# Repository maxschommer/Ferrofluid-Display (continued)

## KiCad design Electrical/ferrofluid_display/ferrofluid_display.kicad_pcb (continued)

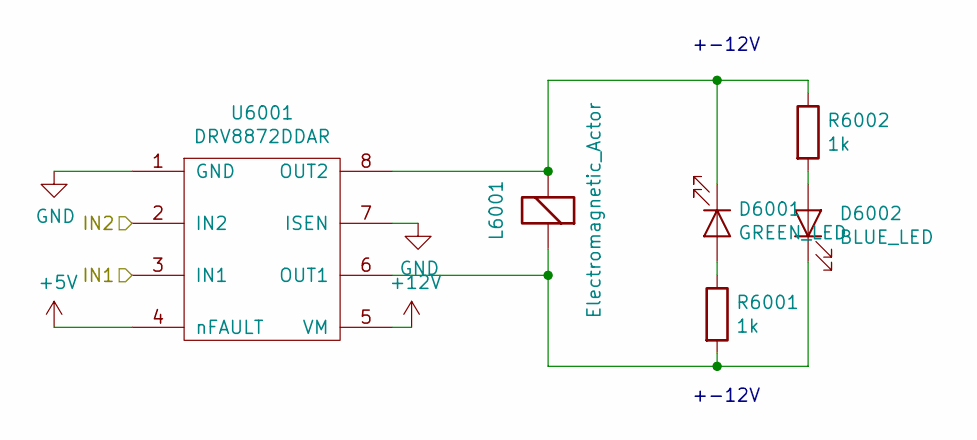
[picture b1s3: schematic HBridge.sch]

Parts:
D6001: GREEN_LED; LED_0805
D6002: BLUE_LED; LED_0805
L6001: Electromagnetic_Actor; ElectroMagnet
R6001, R6002: 1k; R_0603
U6001: DRV8872DDAR; TI_SO-PowerPAD-8_ThermalVias

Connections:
+5V: U6001.4 (nFAULT); also elsewhere on the board
+12V: U6001.5 (VM); also elsewhere on the board
/O_1: U6001.3 (IN1); also elsewhere on the board
/O_2: U6001.2 (IN2); also elsewhere on the board
GND: U6001.1 (GND), U6001.7 (ISEN); also elsewhere on the board
unnamed: D6001.1 (K), L6001.2 (+), R6002.1, U6001.8 (OUT2)
unnamed: D6001.2 (A), R6001.1
unnamed: D6002.1 (K), L6001.1 (-), R6001.2, U6001.6 (OUT1)
unnamed: D6002.2 (A), R6002.2

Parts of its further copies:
D7001, D8001, D9001, D10001, D11001, D12001, D13001, D14001, D15001, D17001, D18001, D19001, D20001, D21001, D22001, D23001, D24001, D25001, D26001, D28001, D29001, D30001, D31001, D32001, D33001, D34001, D35001, D36001, D37001, D39001, D40001, D41001, D42001, D43001, D44001, D45001, D46001, D47001, D48001, D50001, D51001, D52001, D53001, D54001, D55001, D56001, D57001, D58001, D59001, D61001, D62001, D63001, D64001, D65001, D66001, D67001, D68001, D69001, D70001, D72001, D73001, D74001, D75001, D76001, D77001, D78001, D79001, D80001, D81001, D83001, D84001, D85001, D86001, D87001, D88001, D89001, D90001, D91001, D92001, D94001, D95001, D96001, D97001, D98001, D99001, D100001, D101001, D102001, D103001, D105001, D106001, D107001, D108001, D109001, D110001, D111001, D112001, D113001, D114001: GREEN_LED; LED_0805
D7002, D8002, D9002, D10002, D11002, D12002, D13002, D14002, D15002, D17002, D18002, D19002, D20002, D21002, D22002, D23002, D24002, D25002, D26002, D28002, D29002, D30002, D31002, D32002, D33002, D34002, D35002, D36002, D37002, D39002, D40002, D41002, D42002, D43002, D44002, D45002, D46002, D47002, D48002, D50002, D51002, D52002, D53002, D54002, D55002, D56002, D57002, D58002, D59002, D61002, D62002, D63002, D64002, D65002, D66002, D67002, D68002, D69002, D70002, D72002, D73002, D74002, D75002, D76002, D77002, D78002, D79002, D80002, D81002, D83002, D84002, D85002, D86002, D87002, D88002, D89002, D90002, D91002, D92002, D94002, D95002, D96002, D97002, D98002, D99002, D100002, D101002, D102002, D103002, D105002, D106002, D107002, D108002, D109002, D110002, D111002, D112002, D113002, D114002: BLUE_LED; LED_0805
L7001, L8001, L9001, L10001, L11001, L12001, L13001, L14001, L15001, L17001, L18001, L19001, L20001, L21001, L22001, L23001, L24001, L25001, L26001, L28001, L29001, L30001, L31001, L32001, L33001, L34001, L35001, L36001, L37001, L39001, L40001, L41001, L42001, L43001, L44001, L45001, L46001, L47001, L48001, L50001, L51001, L52001, L53001, L54001, L55001, L56001, L57001, L58001, L59001, L61001, L62001, L63001, L64001, L65001, L66001, L67001, L68001, L69001, L70001, L72001, L73001, L74001, L75001, L76001, L77001, L78001, L79001, L80001, L81001, L83001, L84001, L85001, L86001, L87001, L88001, L89001, L90001, L91001, L92001, L94001, L95001, L96001, L97001, L98001, L99001, L100001, L101001, L102001, L103001, L105001, L106001, L107001, L108001, L109001, L110001, L111001, L112001, L113001, L114001: Electromagnetic_Actor; ElectroMagnet
R7001, R7002, R8001, R8002, R9001, R9002, R10001, R10002, R11001, R11002, R12001, R12002, R13001, R13002, R14001, R14002, R15001, R15002, R17001, R17002, R18001, R18002, R19001, R19002, R20001, R20002, R21001, R21002, R22001, R22002, R23001, R23002, R24001, R24002, R25001, R25002, R26001, R26002, R28001, R28002, R29001, R29002, R30001, R30002, R31001, R31002, R32001, R32002, R33001, R33002, R34001, R34002, R35001, R35002, R36001, R36002, R37001, R37002, R39001, R39002, R40001, R40002, R41001, R41002, R42001, R42002, R43001, R43002, R44001, R44002, R45001, R45002, R46001, R46002, R47001, R47002, R48001, R48002, R50001, R50002, R51001, R51002, R52001, R52002, R53001, R53002, R54001, R54002, R55001, R55002, R56001, R56002, R57001, R57002, R58001, R58002, R59001, R59002, R61001, R61002, R62001, R62002, R63001, R63002, R64001, R64002, R65001, R65002, R66001, R66002, R67001, R67002, R68001, R68002, R69001, R69002, R70001, R70002, R72001, R72002, R73001, R73002, R74001, R74002, R75001, R75002, R76001, R76002, R77001, R77002, R78001, R78002, R79001, R79002, R80001, R80002, R81001, R81002, R83001, R83002, R84001, R84002, R85001, R85002, R86001, R86002, R87001, R87002, R88001, R88002, R89001, R89002, R90001, R90002, R91001, R91002, R92001, R92002, R94001, R94002, R95001, R95002, R96001, R96002, R97001, R97002, R98001, R98002, R99001, R99002, R100001, R100002, R101001, R101002, R102001, R102002, R103001, R103002, R105001, R105002, R106001, R106002, R107001, R107002, R108001, R108002, R109001, R109002, R110001, R110002, R111001, R111002, R112001, R112002, R113001, R113002, R114001, R114002: 1k; R_0603
U7001, U8001, U9001, U10001, U11001, U12001, U13001, U14001, U15001, U17001, U18001, U19001, U20001, U21001, U22001, U23001, U24001, U25001, U26001, U28001, U29001, U30001, U31001, U32001, U33001, U34001, U35001, U36001, U37001, U39001, U40001, U41001, U42001, U43001, U44001, U45001, U46001, U47001, U48001, U50001, U51001, U52001, U53001, U54001, U55001, U56001, U57001, U58001, U59001, U61001, U62001, U63001, U64001, U65001, U66001, U67001, U68001, U69001, U70001, U72001, U73001, U74001, U75001, U76001, U77001, U78001, U79001, U80001, U81001, U83001, U84001, U85001, U86001, U87001, U88001, U89001, U90001, U91001, U92001, U94001, U95001, U96001, U97001, U98001, U99001, U100001, U101001, U102001, U103001, U105001, U106001, U107001, U108001, U109001, U110001, U111001, U112001, U113001, U114001: DRV8872DDAR; TI_SO-PowerPAD-8_ThermalVias

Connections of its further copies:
+5V: U7001.4 (nFAULT), U8001.4 (nFAULT), U9001.4 (nFAULT), U10001.4 (nFAULT), U11001.4 (nFAULT), U12001.4 (nFAULT), U13001.4 (nFAULT), U14001.4 (nFAULT), U15001.4 (nFAULT), U17001.4 (nFAULT), U18001.4 (nFAULT), U19001.4 (nFAULT), U20001.4 (nFAULT), U21001.4 (nFAULT), U22001.4 (nFAULT), U23001.4 (nFAULT), U24001.4 (nFAULT), U25001.4 (nFAULT), U26001.4 (nFAULT), U28001.4 (nFAULT), U29001.4 (nFAULT), U30001.4 (nFAULT), U31001.4 (nFAULT), U32001.4 (nFAULT), U33001.4 (nFAULT), U34001.4 (nFAULT), U35001.4 (nFAULT), U36001.4 (nFAULT), U37001.4 (nFAULT), U39001.4 (nFAULT), U40001.4 (nFAULT), U41001.4 (nFAULT), U42001.4 (nFAULT), U43001.4 (nFAULT), U44001.4 (nFAULT), U45001.4 (nFAULT), U46001.4 (nFAULT), U47001.4 (nFAULT), U48001.4 (nFAULT), U50001.4 (nFAULT), U51001.4 (nFAULT), U52001.4 (nFAULT), U53001.4 (nFAULT), U54001.4 (nFAULT), U55001.4 (nFAULT), U56001.4 (nFAULT), U57001.4 (nFAULT), U58001.4 (nFAULT), U59001.4 (nFAULT), U61001.4 (nFAULT), U62001.4 (nFAULT), U63001.4 (nFAULT), U64001.4 (nFAULT), U65001.4 (nFAULT), U66001.4 (nFAULT), U67001.4 (nFAULT), U68001.4 (nFAULT), U69001.4 (nFAULT), U70001.4 (nFAULT), U72001.4 (nFAULT), U73001.4 (nFAULT), U74001.4 (nFAULT), U75001.4 (nFAULT), U76001.4 (nFAULT), U77001.4 (nFAULT), U78001.4 (nFAULT), U79001.4 (nFAULT), U80001.4 (nFAULT), U81001.4 (nFAULT), U83001.4 (nFAULT), U84001.4 (nFAULT), U85001.4 (nFAULT), U86001.4 (nFAULT), U87001.4 (nFAULT), U88001.4 (nFAULT), U89001.4 (nFAULT), U90001.4 (nFAULT), U91001.4 (nFAULT), U92001.4 (nFAULT), U94001.4 (nFAULT), U95001.4 (nFAULT), U96001.4 (nFAULT), U97001.4 (nFAULT), U98001.4 (nFAULT), U99001.4 (nFAULT), U100001.4 (nFAULT), U101001.4 (nFAULT), U102001.4 (nFAULT), U103001.4 (nFAULT), U105001.4 (nFAULT), U106001.4 (nFAULT), U107001.4 (nFAULT), U108001.4 (nFAULT), U109001.4 (nFAULT), U110001.4 (nFAULT), U111001.4 (nFAULT), U112001.4 (nFAULT), U113001.4 (nFAULT), U114001.4 (nFAULT); also elsewhere on the board
+12V: U7001.5 (VM), U8001.5 (VM), U9001.5 (VM), U10001.5 (VM), U11001.5 (VM), U12001.5 (VM), U13001.5 (VM), U14001.5 (VM), U15001.5 (VM), U17001.5 (VM), U18001.5 (VM), U19001.5 (VM), U20001.5 (VM), U21001.5 (VM), U22001.5 (VM), U23001.5 (VM), U24001.5 (VM), U25001.5 (VM), U26001.5 (VM), U28001.5 (VM), U29001.5 (VM), U30001.5 (VM), U31001.5 (VM), U32001.5 (VM), U33001.5 (VM), U34001.5 (VM), U35001.5 (VM), U36001.5 (VM), U37001.5 (VM), U39001.5 (VM), U40001.5 (VM), U41001.5 (VM), U42001.5 (VM), U43001.5 (VM), U44001.5 (VM), U45001.5 (VM), U46001.5 (VM), U47001.5 (VM), U48001.5 (VM), U50001.5 (VM), U51001.5 (VM), U52001.5 (VM), U53001.5 (VM), U54001.5 (VM), U55001.5 (VM), U56001.5 (VM), U57001.5 (VM), U58001.5 (VM), U59001.5 (VM), U61001.5 (VM), U62001.5 (VM), U63001.5 (VM), U64001.5 (VM), U65001.5 (VM), U66001.5 (VM), U67001.5 (VM), U68001.5 (VM), U69001.5 (VM), U70001.5 (VM), U72001.5 (VM), U73001.5 (VM), U74001.5 (VM), U75001.5 (VM), U76001.5 (VM), U77001.5 (VM), U78001.5 (VM), U79001.5 (VM), U80001.5 (VM), U81001.5 (VM), U83001.5 (VM), U84001.5 (VM), U85001.5 (VM), U86001.5 (VM), U87001.5 (VM), U88001.5 (VM), U89001.5 (VM), U90001.5 (VM), U91001.5 (VM), U92001.5 (VM), U94001.5 (VM), U95001.5 (VM), U96001.5 (VM), U97001.5 (VM), U98001.5 (VM), U99001.5 (VM), U100001.5 (VM), U101001.5 (VM), U102001.5 (VM), U103001.5 (VM), U105001.5 (VM), U106001.5 (VM), U107001.5 (VM), U108001.5 (VM), U109001.5 (VM), U110001.5 (VM), U111001.5 (VM), U112001.5 (VM), U113001.5 (VM), U114001.5 (VM); also elsewhere on the board
/O_3: U7001.3 (IN1); also elsewhere on the board
/O_4: U7001.2 (IN2); also elsewhere on the board
/O_5: U8001.3 (IN1); also elsewhere on the board
/O_6: U8001.2 (IN2); also elsewhere on the board
/O_7: U9001.3 (IN1); also elsewhere on the board
/O_8: U9001.2 (IN2); also elsewhere on the board
/O_9: U10001.3 (IN1); also elsewhere on the board
/O_10: U10001.2 (IN2); also elsewhere on the board
/O_11: U11001.3 (IN1); also elsewhere on the board
/O_12: U11001.2 (IN2); also elsewhere on the board
/O_13: U12001.3 (IN1); also elsewhere on the board
/O_14: U12001.2 (IN2); also elsewhere on the board
/O_15: U13001.3 (IN1); also elsewhere on the board
/O_16: U13001.2 (IN2); also elsewhere on the board
/O_17: U14001.3 (IN1); also elsewhere on the board
/O_18: U14001.2 (IN2); also elsewhere on the board
/O_19: U15001.3 (IN1); also elsewhere on the board
/O_20: U15001.2 (IN2); also elsewhere on the board
/O_21: U61001.3 (IN1); also elsewhere on the board
/O_22: U61001.2 (IN2); also elsewhere on the board
/O_23: U62001.3 (IN1); also elsewhere on the board
/O_24: U62001.2 (IN2); also elsewhere on the board
/O_25: U63001.3 (IN1); also elsewhere on the board
/O_26: U63001.2 (IN2); also elsewhere on the board
/O_27: U64001.3 (IN1); also elsewhere on the board
/O_28: U64001.2 (IN2); also elsewhere on the board
/O_29: U65001.3 (IN1); also elsewhere on the board
/O_30: U65001.2 (IN2); also elsewhere on the board
/O_31: U66001.3 (IN1); also elsewhere on the board
/O_32: U66001.2 (IN2); also elsewhere on the board
/O_33: U67001.3 (IN1); also elsewhere on the board
/O_34: U67001.2 (IN2); also elsewhere on the board
/O_35: U68001.3 (IN1); also elsewhere on the board
/O_36: U68001.2 (IN2); also elsewhere on the board
/O_37: U69001.3 (IN1); also elsewhere on the board
/O_38: U69001.2 (IN2); also elsewhere on the board
/O_39: U70001.3 (IN1); also elsewhere on the board
/O_40: U70001.2 (IN2); also elsewhere on the board
/O_41: U17001.3 (IN1); also elsewhere on the board
/O_42: U17001.2 (IN2); also elsewhere on the board
/O_43: U18001.3 (IN1); also elsewhere on the board
/O_44: U18001.2 (IN2); also elsewhere on the board
/O_45: U19001.3 (IN1); also elsewhere on the board
/O_46: U19001.2 (IN2); also elsewhere on the board
/O_47: U20001.3 (IN1); also elsewhere on the board
/O_48: U20001.2 (IN2); also elsewhere on the board
/O_49: U21001.3 (IN1); also elsewhere on the board
/O_50: U21001.2 (IN2); also elsewhere on the board
/O_51: U22001.3 (IN1); also elsewhere on the board
/O_52: U22001.2 (IN2); also elsewhere on the board
/O_53: U23001.3 (IN1); also elsewhere on the board
/O_54: U23001.2 (IN2); also elsewhere on the board
/O_55: U24001.3 (IN1); also elsewhere on the board
/O_56: U24001.2 (IN2); also elsewhere on the board
/O_57: U25001.3 (IN1); also elsewhere on the board
/O_58: U25001.2 (IN2); also elsewhere on the board
/O_59: U26001.3 (IN1); also elsewhere on the board
/O_60: U26001.2 (IN2); also elsewhere on the board
/O_61: U72001.3 (IN1); also elsewhere on the board
/O_62: U72001.2 (IN2); also elsewhere on the board
/O_63: U73001.3 (IN1); also elsewhere on the board
/O_64: U73001.2 (IN2); also elsewhere on the board
/O_65: U74001.3 (IN1); also elsewhere on the board
/O_66: U74001.2 (IN2); also elsewhere on the board
/O_67: U75001.3 (IN1); also elsewhere on the board
/O_68: U75001.2 (IN2); also elsewhere on the board
/O_69: U76001.3 (IN1); also elsewhere on the board
/O_70: U76001.2 (IN2); also elsewhere on the board
/O_71: U77001.3 (IN1); also elsewhere on the board
/O_72: U77001.2 (IN2); also elsewhere on the board
/O_73: U78001.3 (IN1); also elsewhere on the board
/O_74: U78001.2 (IN2); also elsewhere on the board
/O_75: U79001.3 (IN1); also elsewhere on the board
/O_76: U79001.2 (IN2); also elsewhere on the board
/O_77: U80001.3 (IN1); also elsewhere on the board
/O_78: U80001.2 (IN2); also elsewhere on the board
/O_79: U81001.3 (IN1); also elsewhere on the board
/O_80: U81001.2 (IN2); also elsewhere on the board
/O_81: U28001.3 (IN1); also elsewhere on the board
/O_82: U28001.2 (IN2); also elsewhere on the board
/O_83: U29001.3 (IN1); also elsewhere on the board
/O_84: U29001.2 (IN2); also elsewhere on the board
/O_85: U30001.3 (IN1); also elsewhere on the board
/O_86: U30001.2 (IN2); also elsewhere on the board
/O_87: U31001.3 (IN1); also elsewhere on the board
/O_88: U31001.2 (IN2); also elsewhere on the board
/O_89: U32001.3 (IN1); also elsewhere on the board
/O_90: U32001.2 (IN2); also elsewhere on the board
/O_91: U33001.3 (IN1); also elsewhere on the board
/O_92: U33001.2 (IN2); also elsewhere on the board
/O_93: U34001.3 (IN1); also elsewhere on the board
/O_94: U34001.2 (IN2); also elsewhere on the board
/O_95: U35001.3 (IN1); also elsewhere on the board
/O_96: U35001.2 (IN2); also elsewhere on the board
/O_97: U36001.3 (IN1); also elsewhere on the board
/O_98: U36001.2 (IN2); also elsewhere on the board
/O_99: U37001.3 (IN1); also elsewhere on the board
/O_100: U37001.2 (IN2); also elsewhere on the board
/O_101: U83001.3 (IN1); also elsewhere on the board
/O_102: U83001.2 (IN2); also elsewhere on the board
/O_103: U84001.3 (IN1); also elsewhere on the board
/O_104: U84001.2 (IN2); also elsewhere on the board
/O_105: U85001.3 (IN1); also elsewhere on the board
/O_106: U85001.2 (IN2); also elsewhere on the board
/O_107: U86001.3 (IN1); also elsewhere on the board
/O_108: U86001.2 (IN2); also elsewhere on the board
/O_109: U87001.3 (IN1); also elsewhere on the board
/O_110: U87001.2 (IN2); also elsewhere on the board
/O_111: U88001.3 (IN1); also elsewhere on the board
/O_112: U88001.2 (IN2); also elsewhere on the board
/O_113: U89001.3 (IN1); also elsewhere on the board
/O_114: U89001.2 (IN2); also elsewhere on the board
/O_115: U90001.3 (IN1); also elsewhere on the board
/O_116: U90001.2 (IN2); also elsewhere on the board
/O_117: U91001.3 (IN1); also elsewhere on the board
/O_118: U91001.2 (IN2); also elsewhere on the board
/O_119: U92001.3 (IN1); also elsewhere on the board
/O_120: U92001.2 (IN2); also elsewhere on the board
/O_121: U39001.3 (IN1); also elsewhere on the board
/O_122: U39001.2 (IN2); also elsewhere on the board
/O_123: U40001.3 (IN1); also elsewhere on the board
/O_124: U40001.2 (IN2); also elsewhere on the board
/O_125: U41001.3 (IN1); also elsewhere on the board
/O_126: U41001.2 (IN2); also elsewhere on the board
/O_127: U42001.3 (IN1); also elsewhere on the board
/O_128: U42001.2 (IN2); also elsewhere on the board
/O_129: U43001.3 (IN1); also elsewhere on the board
/O_130: U43001.2 (IN2); also elsewhere on the board
/O_131: U44001.3 (IN1); also elsewhere on the board
/O_132: U44001.2 (IN2); also elsewhere on the board
/O_133: U45001.3 (IN1); also elsewhere on the board
/O_134: U45001.2 (IN2); also elsewhere on the board
/O_135: U46001.3 (IN1); also elsewhere on the board
/O_136: U46001.2 (IN2); also elsewhere on the board
/O_137: U47001.3 (IN1); also elsewhere on the board
/O_138: U47001.2 (IN2); also elsewhere on the board
/O_139: U48001.3 (IN1); also elsewhere on the board
/O_140: U48001.2 (IN2); also elsewhere on the board
/O_141: U94001.3 (IN1); also elsewhere on the board
/O_142: U94001.2 (IN2); also elsewhere on the board
/O_143: U95001.3 (IN1); also elsewhere on the board
/O_144: U95001.2 (IN2); also elsewhere on the board
/O_145: U96001.3 (IN1); also elsewhere on the board
/O_146: U96001.2 (IN2); also elsewhere on the board
/O_147: U97001.3 (IN1); also elsewhere on the board
/O_148: U97001.2 (IN2); also elsewhere on the board
/O_149: U98001.3 (IN1); also elsewhere on the board
/O_150: U98001.2 (IN2); also elsewhere on the board
/O_151: U99001.3 (IN1); also elsewhere on the board
/O_152: U99001.2 (IN2); also elsewhere on the board
/O_153: U100001.3 (IN1); also elsewhere on the board
/O_154: U100001.2 (IN2); also elsewhere on the board
/O_155: U101001.3 (IN1); also elsewhere on the board
/O_156: U101001.2 (IN2); also elsewhere on the board
/O_157: U102001.3 (IN1); also elsewhere on the board
/O_158: U102001.2 (IN2); also elsewhere on the board
/O_159: U103001.3 (IN1); also elsewhere on the board
/O_160: U103001.2 (IN2); also elsewhere on the board
/O_161: U50001.3 (IN1); also elsewhere on the board
/O_162: U50001.2 (IN2); also elsewhere on the board
/O_163: U51001.3 (IN1); also elsewhere on the board
/O_164: U51001.2 (IN2); also elsewhere on the board
/O_165: U52001.3 (IN1); also elsewhere on the board
/O_166: U52001.2 (IN2); also elsewhere on the board
/O_167: U53001.3 (IN1); also elsewhere on the board
/O_168: U53001.2 (IN2); also elsewhere on the board
/O_169: U54001.3 (IN1); also elsewhere on the board
/O_170: U54001.2 (IN2); also elsewhere on the board
/O_171: U55001.3 (IN1); also elsewhere on the board
/O_172: U55001.2 (IN2); also elsewhere on the board
/O_173: U56001.3 (IN1); also elsewhere on the board
/O_174: U56001.2 (IN2); also elsewhere on the board
/O_175: U57001.3 (IN1); also elsewhere on the board
/O_176: U57001.2 (IN2); also elsewhere on the board
/O_177: U58001.3 (IN1); also elsewhere on the board
/O_178: U58001.2 (IN2); also elsewhere on the board
/O_179: U59001.3 (IN1); also elsewhere on the board
/O_180: U59001.2 (IN2); also elsewhere on the board
/O_181: U105001.3 (IN1); also elsewhere on the board
/O_182: U105001.2 (IN2); also elsewhere on the board
/O_183: U106001.3 (IN1); also elsewhere on the board
/O_184: U106001.2 (IN2); also elsewhere on the board
/O_185: U107001.3 (IN1); also elsewhere on the board
/O_186: U107001.2 (IN2); also elsewhere on the board
/O_187: U108001.3 (IN1); also elsewhere on the board
/O_188: U108001.2 (IN2); also elsewhere on the board
/O_189: U109001.3 (IN1); also elsewhere on the board
/O_190: U109001.2 (IN2); also elsewhere on the board
/O_191: U110001.3 (IN1); also elsewhere on the board
/O_192: U110001.2 (IN2); also elsewhere on the board
/O_193: U111001.3 (IN1); also elsewhere on the board
/O_194: U111001.2 (IN2); also elsewhere on the board
/O_195: U112001.3 (IN1); also elsewhere on the board
/O_196: U112001.2 (IN2); also elsewhere on the board
/O_197: U113001.3 (IN1); also elsewhere on the board
/O_198: U113001.2 (IN2); also elsewhere on the board
/O_199: U114001.3 (IN1); also elsewhere on the board
/O_200: U114001.2 (IN2); also elsewhere on the board
GND: U7001.1 (GND), U7001.7 (ISEN), U8001.1 (GND), U8001.7 (ISEN), U9001.1 (GND), U9001.7 (ISEN), U10001.1 (GND), U10001.7 (ISEN), U11001.1 (GND), U11001.7 (ISEN), U12001.1 (GND), U12001.7 (ISEN), U13001.1 (GND), U13001.7 (ISEN), U14001.1 (GND), U14001.7 (ISEN), U15001.1 (GND), U15001.7 (ISEN), U17001.1 (GND), U17001.7 (ISEN), U18001.1 (GND), U18001.7 (ISEN), U19001.1 (GND), U19001.7 (ISEN), U20001.1 (GND), U20001.7 (ISEN), U21001.1 (GND), U21001.7 (ISEN), U22001.1 (GND), U22001.7 (ISEN), U23001.1 (GND), U23001.7 (ISEN), U24001.1 (GND), U24001.7 (ISEN), U25001.1 (GND), U25001.7 (ISEN), U26001.1 (GND), U26001.7 (ISEN), U28001.1 (GND), U28001.7 (ISEN), U29001.1 (GND), U29001.7 (ISEN), U30001.1 (GND), U30001.7 (ISEN), U31001.1 (GND), U31001.7 (ISEN), U32001.1 (GND), U32001.7 (ISEN), U33001.1 (GND), U33001.7 (ISEN), U34001.1 (GND), U34001.7 (ISEN), U35001.1 (GND), U35001.7 (ISEN), U36001.1 (GND), U36001.7 (ISEN), U37001.1 (GND), U37001.7 (ISEN), U39001.1 (GND), U39001.7 (ISEN), U40001.1 (GND), U40001.7 (ISEN), U41001.1 (GND), U41001.7 (ISEN), U42001.1 (GND), U42001.7 (ISEN), U43001.1 (GND), U43001.7 (ISEN), U44001.1 (GND), U44001.7 (ISEN), U45001.1 (GND), U45001.7 (ISEN), U46001.1 (GND), U46001.7 (ISEN), U47001.1 (GND), U47001.7 (ISEN), U48001.1 (GND), U48001.7 (ISEN), U50001.1 (GND), U50001.7 (ISEN), U51001.1 (GND), U51001.7 (ISEN), U52001.1 (GND), U52001.7 (ISEN), U53001.1 (GND), U53001.7 (ISEN), U54001.1 (GND), U54001.7 (ISEN), U55001.1 (GND), U55001.7 (ISEN), U56001.1 (GND), U56001.7 (ISEN), U57001.1 (GND), U57001.7 (ISEN), U58001.1 (GND), U58001.7 (ISEN), U59001.1 (GND), U59001.7 (ISEN), U61001.1 (GND), U61001.7 (ISEN), U62001.1 (GND), U62001.7 (ISEN), U63001.1 (GND), U63001.7 (ISEN), U64001.1 (GND), U64001.7 (ISEN), U65001.1 (GND), U65001.7 (ISEN), U66001.1 (GND), U66001.7 (ISEN), U67001.1 (GND), U67001.7 (ISEN), U68001.1 (GND), U68001.7 (ISEN), U69001.1 (GND), U69001.7 (ISEN), U70001.1 (GND), U70001.7 (ISEN), U72001.1 (GND), U72001.7 (ISEN), U73001.1 (GND), U73001.7 (ISEN), U74001.1 (GND), U74001.7 (ISEN), U75001.1 (GND), U75001.7 (ISEN), U76001.1 (GND), U76001.7 (ISEN), U77001.1 (GND), U77001.7 (ISEN), U78001.1 (GND), U78001.7 (ISEN), U79001.1 (GND), U79001.7 (ISEN), U80001.1 (GND), U80001.7 (ISEN), U81001.1 (GND), U81001.7 (ISEN), U83001.1 (GND), U83001.7 (ISEN), U84001.1 (GND), U84001.7 (ISEN), U85001.1 (GND), U85001.7 (ISEN), U86001.1 (GND), U86001.7 (ISEN), U87001.1 (GND), U87001.7 (ISEN), U88001.1 (GND), U88001.7 (ISEN), U89001.1 (GND), U89001.7 (ISEN), U90001.1 (GND), U90001.7 (ISEN), U91001.1 (GND), U91001.7 (ISEN), U92001.1 (GND), U92001.7 (ISEN), U94001.1 (GND), U94001.7 (ISEN), U95001.1 (GND), U95001.7 (ISEN), U96001.1 (GND), U96001.7 (ISEN), U97001.1 (GND), U97001.7 (ISEN), U98001.1 (GND), U98001.7 (ISEN), U99001.1 (GND), U99001.7 (ISEN), U100001.1 (GND), U100001.7 (ISEN), U101001.1 (GND), U101001.7 (ISEN), U102001.1 (GND), U102001.7 (ISEN), U103001.1 (GND), U103001.7 (ISEN), U105001.1 (GND), U105001.7 (ISEN), U106001.1 (GND), U106001.7 (ISEN), U107001.1 (GND), U107001.7 (ISEN), U108001.1 (GND), U108001.7 (ISEN), U109001.1 (GND), U109001.7 (ISEN), U110001.1 (GND), U110001.7 (ISEN), U111001.1 (GND), U111001.7 (ISEN), U112001.1 (GND), U112001.7 (ISEN), U113001.1 (GND), U113001.7 (ISEN), U114001.1 (GND), U114001.7 (ISEN); also elsewhere on the board
unnamed: D7001.1 (K), L7001.2 (+), R7002.1, U7001.8 (OUT2)
unnamed: D7001.2 (A), R7001.1
unnamed: D7002.1 (K), L7001.1 (-), R7001.2, U7001.6 (OUT1)
unnamed: D7002.2 (A), R7002.2
unnamed: D8001.1 (K), L8001.2 (+), R8002.1, U8001.8 (OUT2)
unnamed: D8001.2 (A), R8001.1
unnamed: D8002.1 (K), L8001.1 (-), R8001.2, U8001.6 (OUT1)
unnamed: D8002.2 (A), R8002.2
unnamed: D9001.1 (K), L9001.2 (+), R9002.1, U9001.8 (OUT2)
unnamed: D9001.2 (A), R9001.1
unnamed: D9002.1 (K), L9001.1 (-), R9001.2, U9001.6 (OUT1)
unnamed: D9002.2 (A), R9002.2
unnamed: D10001.1 (K), L10001.2 (+), R10002.1, U10001.8 (OUT2)
unnamed: D10001.2 (A), R10001.1
unnamed: D10002.1 (K), L10001.1 (-), R10001.2, U10001.6 (OUT1)
unnamed: D10002.2 (A), R10002.2
unnamed: D11001.1 (K), L11001.2 (+), R11002.1, U11001.8 (OUT2)
unnamed: D11001.2 (A), R11001.1
unnamed: D11002.1 (K), L11001.1 (-), R11001.2, U11001.6 (OUT1)
unnamed: D11002.2 (A), R11002.2
unnamed: D12001.1 (K), L12001.2 (+), R12002.1, U12001.8 (OUT2)
unnamed: D12001.2 (A), R12001.1
unnamed: D12002.1 (K), L12001.1 (-), R12001.2, U12001.6 (OUT1)
unnamed: D12002.2 (A), R12002.2
unnamed: D13001.1 (K), L13001.2 (+), R13002.1, U13001.8 (OUT2)
unnamed: D13001.2 (A), R13001.1
unnamed: D13002.1 (K), L13001.1 (-), R13001.2, U13001.6 (OUT1)
unnamed: D13002.2 (A), R13002.2
unnamed: D14001.1 (K), L14001.2 (+), R14002.1, U14001.8 (OUT2)
unnamed: D14001.2 (A), R14001.1
unnamed: D14002.1 (K), L14001.1 (-), R14001.2, U14001.6 (OUT1)
unnamed: D14002.2 (A), R14002.2
unnamed: D15001.1 (K), L15001.2 (+), R15002.1, U15001.8 (OUT2)
unnamed: D15001.2 (A), R15001.1
unnamed: D15002.1 (K), L15001.1 (-), R15001.2, U15001.6 (OUT1)
unnamed: D15002.2 (A), R15002.2
unnamed: D17001.1 (K), L17001.2 (+), R17002.1, U17001.8 (OUT2)
unnamed: D17001.2 (A), R17001.1
unnamed: D17002.1 (K), L17001.1 (-), R17001.2, U17001.6 (OUT1)
unnamed: D17002.2 (A), R17002.2
unnamed: D18001.1 (K), L18001.2 (+), R18002.1, U18001.8 (OUT2)
unnamed: D18001.2 (A), R18001.1
unnamed: D18002.1 (K), L18001.1 (-), R18001.2, U18001.6 (OUT1)
unnamed: D18002.2 (A), R18002.2
unnamed: D19001.1 (K), L19001.2 (+), R19002.1, U19001.8 (OUT2)
unnamed: D19001.2 (A), R19001.1
unnamed: D19002.1 (K), L19001.1 (-), R19001.2, U19001.6 (OUT1)
unnamed: D19002.2 (A), R19002.2
unnamed: D20001.1 (K), L20001.2 (+), R20002.1, U20001.8 (OUT2)
unnamed: D20001.2 (A), R20001.1
unnamed: D20002.1 (K), L20001.1 (-), R20001.2, U20001.6 (OUT1)
unnamed: D20002.2 (A), R20002.2
unnamed: D21001.1 (K), L21001.2 (+), R21002.1, U21001.8 (OUT2)
unnamed: D21001.2 (A), R21001.1
unnamed: D21002.1 (K), L21001.1 (-), R21001.2, U21001.6 (OUT1)
unnamed: D21002.2 (A), R21002.2
unnamed: D22001.1 (K), L22001.2 (+), R22002.1, U22001.8 (OUT2)
unnamed: D22001.2 (A), R22001.1
unnamed: D22002.1 (K), L22001.1 (-), R22001.2, U22001.6 (OUT1)
unnamed: D22002.2 (A), R22002.2
unnamed: D23001.1 (K), L23001.2 (+), R23002.1, U23001.8 (OUT2)
unnamed: D23001.2 (A), R23001.1
unnamed: D23002.1 (K), L23001.1 (-), R23001.2, U23001.6 (OUT1)
unnamed: D23002.2 (A), R23002.2
unnamed: D24001.1 (K), L24001.2 (+), R24002.1, U24001.8 (OUT2)
unnamed: D24001.2 (A), R24001.1
unnamed: D24002.1 (K), L24001.1 (-), R24001.2, U24001.6 (OUT1)
unnamed: D24002.2 (A), R24002.2
unnamed: D25001.1 (K), L25001.2 (+), R25002.1, U25001.8 (OUT2)
unnamed: D25001.2 (A), R25001.1
unnamed: D25002.1 (K), L25001.1 (-), R25001.2, U25001.6 (OUT1)
unnamed: D25002.2 (A), R25002.2
unnamed: D26001.1 (K), L26001.2 (+), R26002.1, U26001.8 (OUT2)
unnamed: D26001.2 (A), R26001.1
unnamed: D26002.1 (K), L26001.1 (-), R26001.2, U26001.6 (OUT1)
unnamed: D26002.2 (A), R26002.2
unnamed: D28001.1 (K), L28001.2 (+), R28002.1, U28001.8 (OUT2)
unnamed: D28001.2 (A), R28001.1
unnamed: D28002.1 (K), L28001.1 (-), R28001.2, U28001.6 (OUT1)
unnamed: D28002.2 (A), R28002.2
unnamed: D29001.1 (K), L29001.2 (+), R29002.1, U29001.8 (OUT2)
unnamed: D29001.2 (A), R29001.1
unnamed: D29002.1 (K), L29001.1 (-), R29001.2, U29001.6 (OUT1)
unnamed: D29002.2 (A), R29002.2
unnamed: D30001.1 (K), L30001.2 (+), R30002.1, U30001.8 (OUT2)
unnamed: D30001.2 (A), R30001.1
unnamed: D30002.1 (K), L30001.1 (-), R30001.2, U30001.6 (OUT1)
unnamed: D30002.2 (A), R30002.2
unnamed: D31001.1 (K), L31001.2 (+), R31002.1, U31001.8 (OUT2)
unnamed: D31001.2 (A), R31001.1
unnamed: D31002.1 (K), L31001.1 (-), R31001.2, U31001.6 (OUT1)
unnamed: D31002.2 (A), R31002.2
unnamed: D32001.1 (K), L32001.2 (+), R32002.1, U32001.8 (OUT2)
unnamed: D32001.2 (A), R32001.1
unnamed: D32002.1 (K), L32001.1 (-), R32001.2, U32001.6 (OUT1)
unnamed: D32002.2 (A), R32002.2
unnamed: D33001.1 (K), L33001.2 (+), R33002.1, U33001.8 (OUT2)
unnamed: D33001.2 (A), R33001.1
unnamed: D33002.1 (K), L33001.1 (-), R33001.2, U33001.6 (OUT1)
unnamed: D33002.2 (A), R33002.2
unnamed: D34001.1 (K), L34001.2 (+), R34002.1, U34001.8 (OUT2)
unnamed: D34001.2 (A), R34001.1
unnamed: D34002.1 (K), L34001.1 (-), R34001.2, U34001.6 (OUT1)
unnamed: D34002.2 (A), R34002.2
unnamed: D35001.1 (K), L35001.2 (+), R35002.1, U35001.8 (OUT2)
unnamed: D35001.2 (A), R35001.1
unnamed: D35002.1 (K), L35001.1 (-), R35001.2, U35001.6 (OUT1)
unnamed: D35002.2 (A), R35002.2
unnamed: D36001.1 (K), L36001.2 (+), R36002.1, U36001.8 (OUT2)
unnamed: D36001.2 (A), R36001.1
unnamed: D36002.1 (K), L36001.1 (-), R36001.2, U36001.6 (OUT1)
unnamed: D36002.2 (A), R36002.2
unnamed: D37001.1 (K), L37001.2 (+), R37002.1, U37001.8 (OUT2)
unnamed: D37001.2 (A), R37001.1
unnamed: D37002.1 (K), L37001.1 (-), R37001.2, U37001.6 (OUT1)
unnamed: D37002.2 (A), R37002.2
unnamed: D39001.1 (K), L39001.2 (+), R39002.1, U39001.8 (OUT2)
unnamed: D39001.2 (A), R39001.1
unnamed: D39002.1 (K), L39001.1 (-), R39001.2, U39001.6 (OUT1)
unnamed: D39002.2 (A), R39002.2
unnamed: D40001.1 (K), L40001.2 (+), R40002.1, U40001.8 (OUT2)
unnamed: D40001.2 (A), R40001.1
unnamed: D40002.1 (K), L40001.1 (-), R40001.2, U40001.6 (OUT1)
unnamed: D40002.2 (A), R40002.2
unnamed: D41001.1 (K), L41001.2 (+), R41002.1, U41001.8 (OUT2)
unnamed: D41001.2 (A), R41001.1
unnamed: D41002.1 (K), L41001.1 (-), R41001.2, U41001.6 (OUT1)
unnamed: D41002.2 (A), R41002.2
unnamed: D42001.1 (K), L42001.2 (+), R42002.1, U42001.8 (OUT2)
unnamed: D42001.2 (A), R42001.1
unnamed: D42002.1 (K), L42001.1 (-), R42001.2, U42001.6 (OUT1)
unnamed: D42002.2 (A), R42002.2
unnamed: D43001.1 (K), L43001.2 (+), R43002.1, U43001.8 (OUT2)
unnamed: D43001.2 (A), R43001.1
unnamed: D43002.1 (K), L43001.1 (-), R43001.2, U43001.6 (OUT1)
unnamed: D43002.2 (A), R43002.2
unnamed: D44001.1 (K), L44001.2 (+), R44002.1, U44001.8 (OUT2)
unnamed: D44001.2 (A), R44001.1
unnamed: D44002.1 (K), L44001.1 (-), R44001.2, U44001.6 (OUT1)
unnamed: D44002.2 (A), R44002.2
unnamed: D45001.1 (K), L45001.2 (+), R45002.1, U45001.8 (OUT2)
unnamed: D45001.2 (A), R45001.1
unnamed: D45002.1 (K), L45001.1 (-), R45001.2, U45001.6 (OUT1)
unnamed: D45002.2 (A), R45002.2
unnamed: D46001.1 (K), L46001.2 (+), R46002.1, U46001.8 (OUT2)
unnamed: D46001.2 (A), R46001.1
unnamed: D46002.1 (K), L46001.1 (-), R46001.2, U46001.6 (OUT1)
unnamed: D46002.2 (A), R46002.2
unnamed: D47001.1 (K), L47001.2 (+), R47002.1, U47001.8 (OUT2)
unnamed: D47001.2 (A), R47001.1
unnamed: D47002.1 (K), L47001.1 (-), R47001.2, U47001.6 (OUT1)
unnamed: D47002.2 (A), R47002.2
unnamed: D48001.1 (K), L48001.2 (+), R48002.1, U48001.8 (OUT2)
unnamed: D48001.2 (A), R48001.1
unnamed: D48002.1 (K), L48001.1 (-), R48001.2, U48001.6 (OUT1)
unnamed: D48002.2 (A), R48002.2
unnamed: D50001.1 (K), L50001.2 (+), R50002.1, U50001.8 (OUT2)
unnamed: D50001.2 (A), R50001.1
unnamed: D50002.1 (K), L50001.1 (-), R50001.2, U50001.6 (OUT1)
unnamed: D50002.2 (A), R50002.2
unnamed: D51001.1 (K), L51001.2 (+), R51002.1, U51001.8 (OUT2)
unnamed: D51001.2 (A), R51001.1
unnamed: D51002.1 (K), L51001.1 (-), R51001.2, U51001.6 (OUT1)
unnamed: D51002.2 (A), R51002.2
unnamed: D52001.1 (K), L52001.2 (+), R52002.1, U52001.8 (OUT2)
unnamed: D52001.2 (A), R52001.1
unnamed: D52002.1 (K), L52001.1 (-), R52001.2, U52001.6 (OUT1)
unnamed: D52002.2 (A), R52002.2
unnamed: D53001.1 (K), L53001.2 (+), R53002.1, U53001.8 (OUT2)
unnamed: D53001.2 (A), R53001.1
unnamed: D53002.1 (K), L53001.1 (-), R53001.2, U53001.6 (OUT1)
unnamed: D53002.2 (A), R53002.2
unnamed: D54001.1 (K), L54001.2 (+), R54002.1, U54001.8 (OUT2)
unnamed: D54001.2 (A), R54001.1
unnamed: D54002.1 (K), L54001.1 (-), R54001.2, U54001.6 (OUT1)
unnamed: D54002.2 (A), R54002.2
unnamed: D55001.1 (K), L55001.2 (+), R55002.1, U55001.8 (OUT2)
unnamed: D55001.2 (A), R55001.1
unnamed: D55002.1 (K), L55001.1 (-), R55001.2, U55001.6 (OUT1)
unnamed: D55002.2 (A), R55002.2
unnamed: D56001.1 (K), L56001.2 (+), R56002.1, U56001.8 (OUT2)
unnamed: D56001.2 (A), R56001.1
unnamed: D56002.1 (K), L56001.1 (-), R56001.2, U56001.6 (OUT1)
unnamed: D56002.2 (A), R56002.2
unnamed: D57001.1 (K), L57001.2 (+), R57002.1, U57001.8 (OUT2)
unnamed: D57001.2 (A), R57001.1
unnamed: D57002.1 (K), L57001.1 (-), R57001.2, U57001.6 (OUT1)
unnamed: D57002.2 (A), R57002.2
unnamed: D58001.1 (K), L58001.2 (+), R58002.1, U58001.8 (OUT2)
unnamed: D58001.2 (A), R58001.1
unnamed: D58002.1 (K), L58001.1 (-), R58001.2, U58001.6 (OUT1)
unnamed: D58002.2 (A), R58002.2
unnamed: D59001.1 (K), L59001.2 (+), R59002.1, U59001.8 (OUT2)
unnamed: D59001.2 (A), R59001.1
unnamed: D59002.1 (K), L59001.1 (-), R59001.2, U59001.6 (OUT1)
unnamed: D59002.2 (A), R59002.2
unnamed: D61001.1 (K), L61001.2 (+), R61002.1, U61001.8 (OUT2)
unnamed: D61001.2 (A), R61001.1
unnamed: D61002.1 (K), L61001.1 (-), R61001.2, U61001.6 (OUT1)
unnamed: D61002.2 (A), R61002.2
unnamed: D62001.1 (K), L62001.2 (+), R62002.1, U62001.8 (OUT2)
unnamed: D62001.2 (A), R62001.1
unnamed: D62002.1 (K), L62001.1 (-), R62001.2, U62001.6 (OUT1)
unnamed: D62002.2 (A), R62002.2
unnamed: D63001.1 (K), L63001.2 (+), R63002.1, U63001.8 (OUT2)
unnamed: D63001.2 (A), R63001.1
unnamed: D63002.1 (K), L63001.1 (-), R63001.2, U63001.6 (OUT1)
unnamed: D63002.2 (A), R63002.2
unnamed: D64001.1 (K), L64001.2 (+), R64002.1, U64001.8 (OUT2)
unnamed: D64001.2 (A), R64001.1
unnamed: D64002.1 (K), L64001.1 (-), R64001.2, U64001.6 (OUT1)
unnamed: D64002.2 (A), R64002.2
unnamed: D65001.1 (K), L65001.2 (+), R65002.1, U65001.8 (OUT2)
unnamed: D65001.2 (A), R65001.1
unnamed: D65002.1 (K), L65001.1 (-), R65001.2, U65001.6 (OUT1)
unnamed: D65002.2 (A), R65002.2
unnamed: D66001.1 (K), L66001.2 (+), R66002.1, U66001.8 (OUT2)
unnamed: D66001.2 (A), R66001.1
unnamed: D66002.1 (K), L66001.1 (-), R66001.2, U66001.6 (OUT1)
unnamed: D66002.2 (A), R66002.2
unnamed: D67001.1 (K), L67001.2 (+), R67002.1, U67001.8 (OUT2)
unnamed: D67001.2 (A), R67001.1
unnamed: D67002.1 (K), L67001.1 (-), R67001.2, U67001.6 (OUT1)
unnamed: D67002.2 (A), R67002.2
unnamed: D68001.1 (K), L68001.2 (+), R68002.1, U68001.8 (OUT2)
unnamed: D68001.2 (A), R68001.1
unnamed: D68002.1 (K), L68001.1 (-), R68001.2, U68001.6 (OUT1)
unnamed: D68002.2 (A), R68002.2
unnamed: D69001.1 (K), L69001.2 (+), R69002.1, U69001.8 (OUT2)
unnamed: D69001.2 (A), R69001.1
unnamed: D69002.1 (K), L69001.1 (-), R69001.2, U69001.6 (OUT1)
unnamed: D69002.2 (A), R69002.2
unnamed: D70001.1 (K), L70001.2 (+), R70002.1, U70001.8 (OUT2)
unnamed: D70001.2 (A), R70001.1
unnamed: D70002.1 (K), L70001.1 (-), R70001.2, U70001.6 (OUT1)
unnamed: D70002.2 (A), R70002.2
unnamed: D72001.1 (K), L72001.2 (+), R72002.1, U72001.8 (OUT2)
unnamed: D72001.2 (A), R72001.1
unnamed: D72002.1 (K), L72001.1 (-), R72001.2, U72001.6 (OUT1)
unnamed: D72002.2 (A), R72002.2
unnamed: D73001.1 (K), L73001.2 (+), R73002.1, U73001.8 (OUT2)
unnamed: D73001.2 (A), R73001.1
unnamed: D73002.1 (K), L73001.1 (-), R73001.2, U73001.6 (OUT1)
unnamed: D73002.2 (A), R73002.2
unnamed: D74001.1 (K), L74001.2 (+), R74002.1, U74001.8 (OUT2)
unnamed: D74001.2 (A), R74001.1
unnamed: D74002.1 (K), L74001.1 (-), R74001.2, U74001.6 (OUT1)
unnamed: D74002.2 (A), R74002.2
unnamed: D75001.1 (K), L75001.2 (+), R75002.1, U75001.8 (OUT2)
unnamed: D75001.2 (A), R75001.1
unnamed: D75002.1 (K), L75001.1 (-), R75001.2, U75001.6 (OUT1)
unnamed: D75002.2 (A), R75002.2
unnamed: D76001.1 (K), L76001.2 (+), R76002.1, U76001.8 (OUT2)
unnamed: D76001.2 (A), R76001.1
unnamed: D76002.1 (K), L76001.1 (-), R76001.2, U76001.6 (OUT1)
unnamed: D76002.2 (A), R76002.2
unnamed: D77001.1 (K), L77001.2 (+), R77002.1, U77001.8 (OUT2)
unnamed: D77001.2 (A), R77001.1
unnamed: D77002.1 (K), L77001.1 (-), R77001.2, U77001.6 (OUT1)
unnamed: D77002.2 (A), R77002.2
unnamed: D78001.1 (K), L78001.2 (+), R78002.1, U78001.8 (OUT2)
unnamed: D78001.2 (A), R78001.1
unnamed: D78002.1 (K), L78001.1 (-), R78001.2, U78001.6 (OUT1)
unnamed: D78002.2 (A), R78002.2
unnamed: D79001.1 (K), L79001.2 (+), R79002.1, U79001.8 (OUT2)
unnamed: D79001.2 (A), R79001.1
unnamed: D79002.1 (K), L79001.1 (-), R79001.2, U79001.6 (OUT1)
unnamed: D79002.2 (A), R79002.2
unnamed: D80001.1 (K), L80001.2 (+), R80002.1, U80001.8 (OUT2)
unnamed: D80001.2 (A), R80001.1
unnamed: D80002.1 (K), L80001.1 (-), R80001.2, U80001.6 (OUT1)
unnamed: D80002.2 (A), R80002.2
unnamed: D81001.1 (K), L81001.2 (+), R81002.1, U81001.8 (OUT2)
unnamed: D81001.2 (A), R81001.1
unnamed: D81002.1 (K), L81001.1 (-), R81001.2, U81001.6 (OUT1)
unnamed: D81002.2 (A), R81002.2
unnamed: D83001.1 (K), L83001.2 (+), R83002.1, U83001.8 (OUT2)
unnamed: D83001.2 (A), R83001.1
unnamed: D83002.1 (K), L83001.1 (-), R83001.2, U83001.6 (OUT1)
unnamed: D83002.2 (A), R83002.2
unnamed: D84001.1 (K), L84001.2 (+), R84002.1, U84001.8 (OUT2)
unnamed: D84001.2 (A), R84001.1
unnamed: D84002.1 (K), L84001.1 (-), R84001.2, U84001.6 (OUT1)
unnamed: D84002.2 (A), R84002.2
unnamed: D85001.1 (K), L85001.2 (+), R85002.1, U85001.8 (OUT2)
unnamed: D85001.2 (A), R85001.1
unnamed: D85002.1 (K), L85001.1 (-), R85001.2, U85001.6 (OUT1)
unnamed: D85002.2 (A), R85002.2
unnamed: D86001.1 (K), L86001.2 (+), R86002.1, U86001.8 (OUT2)
unnamed: D86001.2 (A), R86001.1
unnamed: D86002.1 (K), L86001.1 (-), R86001.2, U86001.6 (OUT1)
unnamed: D86002.2 (A), R86002.2
unnamed: D87001.1 (K), L87001.2 (+), R87002.1, U87001.8 (OUT2)
unnamed: D87001.2 (A), R87001.1
unnamed: D87002.1 (K), L87001.1 (-), R87001.2, U87001.6 (OUT1)
unnamed: D87002.2 (A), R87002.2
unnamed: D88001.1 (K), L88001.2 (+), R88002.1, U88001.8 (OUT2)
unnamed: D88001.2 (A), R88001.1
unnamed: D88002.1 (K), L88001.1 (-), R88001.2, U88001.6 (OUT1)
unnamed: D88002.2 (A), R88002.2
unnamed: D89001.1 (K), L89001.2 (+), R89002.1, U89001.8 (OUT2)
unnamed: D89001.2 (A), R89001.1
unnamed: D89002.1 (K), L89001.1 (-), R89001.2, U89001.6 (OUT1)
unnamed: D89002.2 (A), R89002.2
unnamed: D90001.1 (K), L90001.2 (+), R90002.1, U90001.8 (OUT2)
unnamed: D90001.2 (A), R90001.1
unnamed: D90002.1 (K), L90001.1 (-), R90001.2, U90001.6 (OUT1)
unnamed: D90002.2 (A), R90002.2
unnamed: D91001.1 (K), L91001.2 (+), R91002.1, U91001.8 (OUT2)
unnamed: D91001.2 (A), R91001.1
unnamed: D91002.1 (K), L91001.1 (-), R91001.2, U91001.6 (OUT1)
unnamed: D91002.2 (A), R91002.2
unnamed: D92001.1 (K), L92001.2 (+), R92002.1, U92001.8 (OUT2)
unnamed: D92001.2 (A), R92001.1
unnamed: D92002.1 (K), L92001.1 (-), R92001.2, U92001.6 (OUT1)
unnamed: D92002.2 (A), R92002.2
unnamed: D94001.1 (K), L94001.2 (+), R94002.1, U94001.8 (OUT2)
unnamed: D94001.2 (A), R94001.1
unnamed: D94002.1 (K), L94001.1 (-), R94001.2, U94001.6 (OUT1)
unnamed: D94002.2 (A), R94002.2
unnamed: D95001.1 (K), L95001.2 (+), R95002.1, U95001.8 (OUT2)
unnamed: D95001.2 (A), R95001.1
unnamed: D95002.1 (K), L95001.1 (-), R95001.2, U95001.6 (OUT1)
unnamed: D95002.2 (A), R95002.2
unnamed: D96001.1 (K), L96001.2 (+), R96002.1, U96001.8 (OUT2)
unnamed: D96001.2 (A), R96001.1
unnamed: D96002.1 (K), L96001.1 (-), R96001.2, U96001.6 (OUT1)
unnamed: D96002.2 (A), R96002.2
unnamed: D97001.1 (K), L97001.2 (+), R97002.1, U97001.8 (OUT2)
unnamed: D97001.2 (A), R97001.1
unnamed: D97002.1 (K), L97001.1 (-), R97001.2, U97001.6 (OUT1)
unnamed: D97002.2 (A), R97002.2
unnamed: D98001.1 (K), L98001.2 (+), R98002.1, U98001.8 (OUT2)
unnamed: D98001.2 (A), R98001.1
unnamed: D98002.1 (K), L98001.1 (-), R98001.2, U98001.6 (OUT1)
unnamed: D98002.2 (A), R98002.2
unnamed: D99001.1 (K), L99001.2 (+), R99002.1, U99001.8 (OUT2)
unnamed: D99001.2 (A), R99001.1
unnamed: D99002.1 (K), L99001.1 (-), R99001.2, U99001.6 (OUT1)
unnamed: D99002.2 (A), R99002.2
unnamed: D100001.1 (K), L100001.2 (+), R100002.1, U100001.8 (OUT2)
unnamed: D100001.2 (A), R100001.1
unnamed: D100002.1 (K), L100001.1 (-), R100001.2, U100001.6 (OUT1)
unnamed: D100002.2 (A), R100002.2
unnamed: D101001.1 (K), L101001.2 (+), R101002.1, U101001.8 (OUT2)
unnamed: D101001.2 (A), R101001.1
unnamed: D101002.1 (K), L101001.1 (-), R101001.2, U101001.6 (OUT1)
unnamed: D101002.2 (A), R101002.2
unnamed: D102001.1 (K), L102001.2 (+), R102002.1, U102001.8 (OUT2)
unnamed: D102001.2 (A), R102001.1
unnamed: D102002.1 (K), L102001.1 (-), R102001.2, U102001.6 (OUT1)
unnamed: D102002.2 (A), R102002.2
unnamed: D103001.1 (K), L103001.2 (+), R103002.1, U103001.8 (OUT2)
unnamed: D103001.2 (A), R103001.1
unnamed: D103002.1 (K), L103001.1 (-), R103001.2, U103001.6 (OUT1)
unnamed: D103002.2 (A), R103002.2
unnamed: D105001.1 (K), L105001.2 (+), R105002.1, U105001.8 (OUT2)
unnamed: D105001.2 (A), R105001.1
unnamed: D105002.1 (K), L105001.1 (-), R105001.2, U105001.6 (OUT1)
unnamed: D105002.2 (A), R105002.2
unnamed: D106001.1 (K), L106001.2 (+), R106002.1, U106001.8 (OUT2)
unnamed: D106001.2 (A), R106001.1
unnamed: D106002.1 (K), L106001.1 (-), R106001.2, U106001.6 (OUT1)
unnamed: D106002.2 (A), R106002.2
unnamed: D107001.1 (K), L107001.2 (+), R107002.1, U107001.8 (OUT2)
unnamed: D107001.2 (A), R107001.1
unnamed: D107002.1 (K), L107001.1 (-), R107001.2, U107001.6 (OUT1)
unnamed: D107002.2 (A), R107002.2
unnamed: D108001.1 (K), L108001.2 (+), R108002.1, U108001.8 (OUT2)
unnamed: D108001.2 (A), R108001.1
unnamed: D108002.1 (K), L108001.1 (-), R108001.2, U108001.6 (OUT1)
unnamed: D108002.2 (A), R108002.2
unnamed: D109001.1 (K), L109001.2 (+), R109002.1, U109001.8 (OUT2)
unnamed: D109001.2 (A), R109001.1
unnamed: D109002.1 (K), L109001.1 (-), R109001.2, U109001.6 (OUT1)
unnamed: D109002.2 (A), R109002.2
unnamed: D110001.1 (K), L110001.2 (+), R110002.1, U110001.8 (OUT2)
unnamed: D110001.2 (A), R110001.1
unnamed: D110002.1 (K), L110001.1 (-), R110001.2, U110001.6 (OUT1)
unnamed: D110002.2 (A), R110002.2
unnamed: D111001.1 (K), L111001.2 (+), R111002.1, U111001.8 (OUT2)
unnamed: D111001.2 (A), R111001.1
unnamed: D111002.1 (K), L111001.1 (-), R111001.2, U111001.6 (OUT1)
unnamed: D111002.2 (A), R111002.2
unnamed: D112001.1 (K), L112001.2 (+), R112002.1, U112001.8 (OUT2)
unnamed: D112001.2 (A), R112001.1
unnamed: D112002.1 (K), L112001.1 (-), R112001.2, U112001.6 (OUT1)
unnamed: D112002.2 (A), R112002.2
unnamed: D113001.1 (K), L113001.2 (+), R113002.1, U113001.8 (OUT2)
unnamed: D113001.2 (A), R113001.1
unnamed: D113002.1 (K), L113001.1 (-), R113001.2, U113001.6 (OUT1)
unnamed: D113002.2 (A), R113002.2
unnamed: D114001.1 (K), L114001.2 (+), R114002.1, U114001.8 (OUT2)
unnamed: D114001.2 (A), R114001.1
unnamed: D114002.1 (K), L114001.1 (-), R114001.2, U114001.6 (OUT1)
unnamed: D114002.2 (A), R114002.2

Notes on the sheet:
+-12V

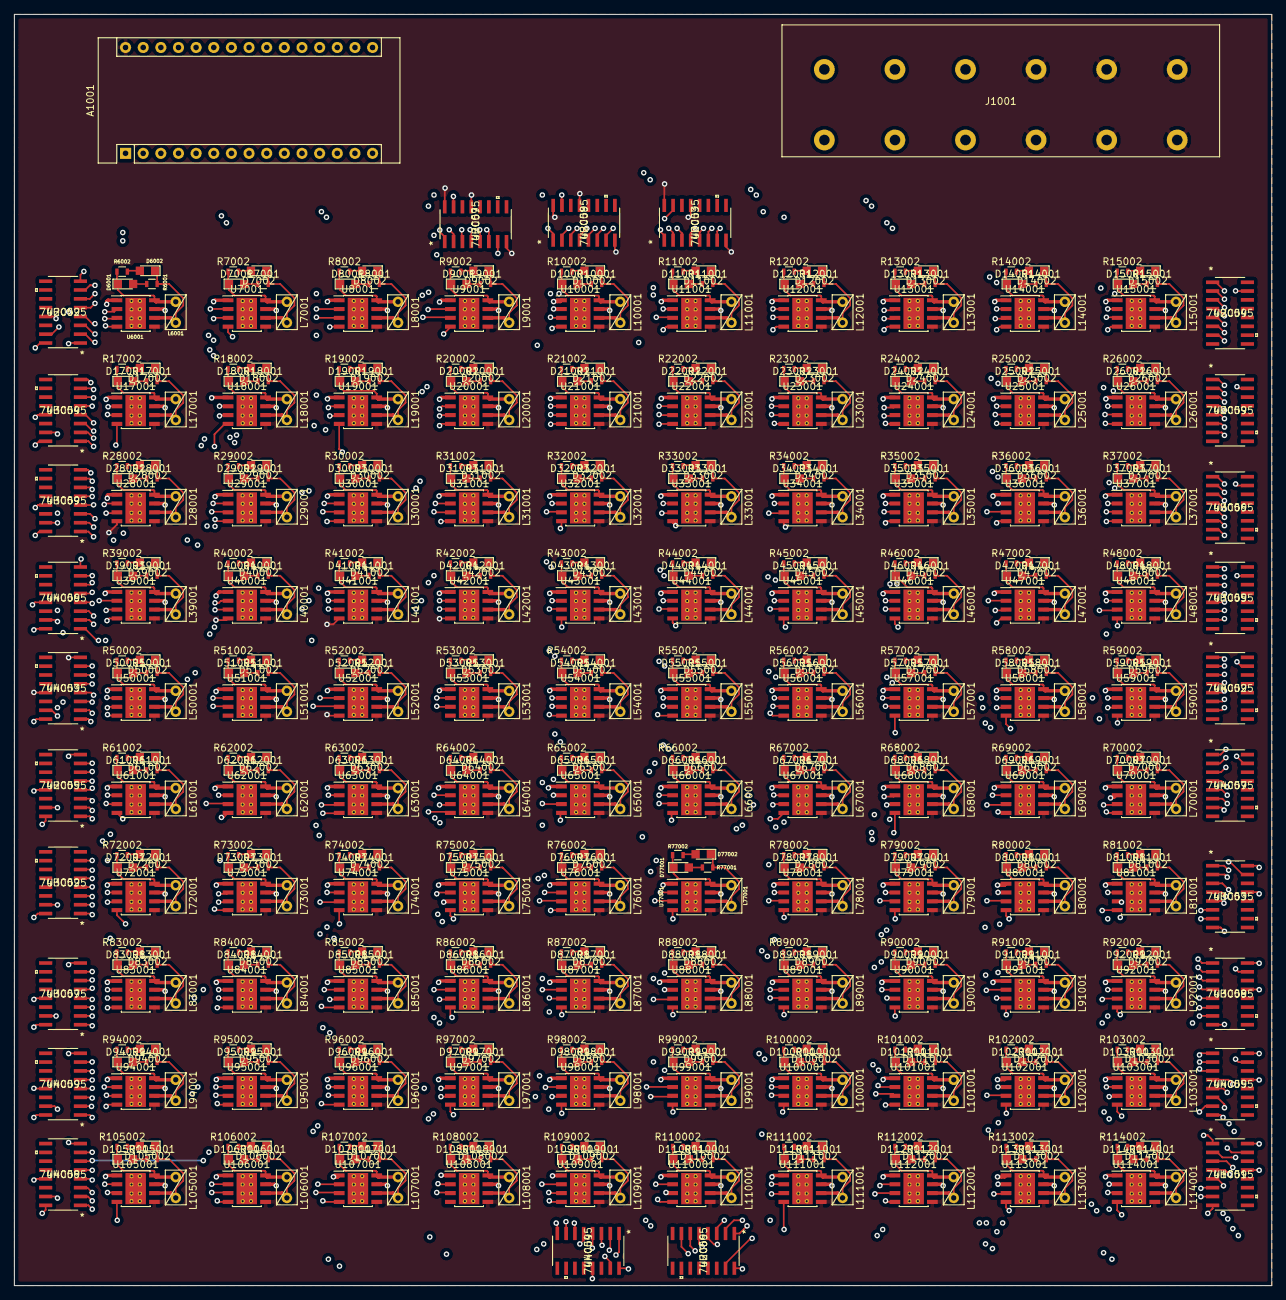
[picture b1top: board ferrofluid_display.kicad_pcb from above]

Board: 4 copper layers, 181.0 x 183.0 mm, 627 parts (0 on the bottom side), 631 nets.

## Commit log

2018-11-05 Made optimization script for electromagnet
2018-11-05 Optimized more
2018-12-15 Schematic complete, layout starting
2018-12-16 Started scripting
2018-12-16 Opened in nightly
2018-12-16 Auto-layed out file
2018-12-16 Added layers and 5V via
2018-12-16 Propegated 5V changes
2018-12-18 Routed most of bord
2018-12-18 Finished routing and text placement
2018-12-19 Rev 1 shipped
